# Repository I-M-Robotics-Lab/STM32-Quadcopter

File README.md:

# STM32-Quadcopter: Low-cost Quadcopter Design

### Description

**[Website](https://www.imroboticslab.com/releases)** | **[Documentation](https://www.imroboticslab.com/docs/stm32-quadcopter)**  | **[Community Discord](https://discord.com/invite/WJuUWsy6DJ)** | **[3D Models & Prints](https://makerworld.com/en/models/1695470-quadcopter-3d-printable-stm32-mcu#profileId-1797658)**

This is a quadcopter design based on the STM32F411CEU Blackpill flight controller. The flight controller is compatible with INAV 6.0 firmware. The flight controller uses an MPU6500 for inertial measurements and a BMP280 for altitude sensing, and also supports an optional GPS and magnetometer module.

The frame is composed mostly of 2D parts cut from carbon-fiber sheets. Alternatively, you can 3D-print parts in carbon-fiber-reinforced filaments (PET-CF, PAHT-CF, PA6-CF, PPS-CF), with less-critical components in ABS.

|  |
| --- |

|  |  |
| --- | --- |

|  |  |
| --- | --- |

---

## Table of Contents

- [Introduction](#stm32-quadcopter-low-cost-quadcopter-design)
- [Frame](#frame)
  - [CF Components](#cf-components)
  - [ABS Components](#abs-components)
  - [Mechanical Components BOM](#mechanical-components-bom)
- [Electronics](#electronics)
  - [Electronics BOM](#electronics-bom)
  - [SMD Components](#smd-components)
  - [Pins](#pins)
  - [Sample Diagram](#sample-diagram)
  - [GPS (UART1) Wiring](#gps-uart1-wiring)
  - [Capacitor for Spike Filtering](#capacitor-for-spike-filtering)
- [Firmware](#firmware)
  - [Build](#build)
    - [Prerequisites](#prerequisites)
    - [Clone INAV](#clone-inav)
    - [Add Target](#add-target)
    - [Patch Code](#patch-code)
    - [Build](#build-1)
  - [Flash](#flash)
  - [MPU9250 Issue](#mpu9250-issue)
- [Configuration and Setting Up](#configuration-and-setting-up)

---

## Frame

Use the assembled CAD model in the `3.Models/` folder as a reference to build.

### CF Components

*All files are under `3.Models/`. Add dogbones and tolerances for manufacturability.*

### ABS Components

*Recommend using a 0.4 mm or 0.6 mm high-strength print profile.*

**Mechanical Components BOM**

| Item Name                   | Qty |
|----------------------------|-----|
| M3 Hex Nut                 | 19  |
| M3 x 12mm Button Head Bolt | 2   |
| M3 x 20mm Button Head Bolt | 7   |
| M3 x 20mm Socket Head Bolt | 6   |
| M3 x 30mm Socket Head Bolt | 16  |
| M3 x 35mm Button Head Bolt | 3   |
| M3 x 40mm Button Head Bolt | 1   |
| Nylon Spacer 3-5-11.2            | 8   |
| Nylon Spacer 3-5-20              | 16  |
| Nylon Spacer 3-5-30              | 4   |
| Nylon Spacer 3-5-5               | 2   |

---
## Electronics

**Structure**
```text
1. Electronics/
  ├── Extra/
  │   ├── *.step
  │   └── ...
  ├── Hardware-backups/
  │   └── ...
  ├── Production/           ← Gerber output for fabrication
  │   ├── Hardware-B_Cu.gbl
  │   └── ...
  ├── Hardware.kicad_pcb    ← KiCAD PCB file
  ├── Hardware.kicad_sch    ← KiCAD Schematics file
  ├── Hardware.kicad_pro    ← KiCAD project
  ├── JLCPCB.kicad_dru      ← Rules for JLCPCB manufacturing
  ├── Production.zip        ← Gerber
  └── Schematics.pdf        ← Schematics
```

### Electronics BOM

| Component                        | Qty |
|----------------------------------|:---:|
| RS2205 BLDC Motor                | 4   |
| BLHeli_S 20A ESC                 | 4   |
| 5030R Propeller                  | 2   |
| STM32F411CEU6 “Blackpill”            | 1   |
| MPU6500 / MPU9250 Module            | 1   |
| BMP280 Module        | 1   |
| 330 µF @ 50 V Capacitor           | 1   |
| FS-iA6B Receiver                 | 1   |
| FS-iA6B Transmitter              | 1   |
| Ovonic 1500 mAh 120C 3s Battery | 1   |
| XT60 Connector                   | 1   |

### SMD Components

Gerber files and BOM are available under the electronics folder.

### Pins

### Sample Diagram

*Diagram only; not actual wiring. Please follow the strict pin assignments.*

### GPS (UART1) Wiring

Ensure connectors are wired correctly according to the pinout. Note that RX should connect to TX: `RX1` → GPS `TX`, `TX1` → GPS `RX`.

### Capacitor for Spike Filtering

One or more bulk electrolytic capacitor is recommended to protect against voltage spikes. Use an electrolytic capacitor such as **330 µF @ 50 V** and place it between `VBAT` and `GND` near the input. For extra protection, a **TVS diode** clampeing at ~**12 V** is ideal.

---
## Firmware

### Build

The firmware used is **INAV v6.0.0 ([github link](https://github.com/iNavFlight/inav))**. This project does not support **INAV v7+** currently due to USB issue. If one wants to modify the target file or other configurations of the firmware, they must rebuild the binary. Follow this guide to build:

**Prerequisites**
- CMake ≥ 3.15  
- Ninja  
- gcc-arm-none-eabi toolchain 

**Clone INAV**
```shell
git clone https://github.com/iNavFlight/inav.git
cd inav
git checkout 6.0
```

**Add Target**

Copy the entire `2.Firmware/GYW_BLACKPILL_F411` folder into the local INAV repository under `src/main/target/` so that it ends up as:

```text
inav/
└── src/
    └── main/
        └── target/
            ├──  GYW_BLACKPILL_F411/
            └── ...
```

**Patch Code**

INAV 6.0 doesn’t support a **25 MHz HSE clock** by default, so if your board (like the **Blackpill F411**) uses a 25 MHz crystal, you must update the PLL setup in `src/main/target/system_stm32f4xx.c` as follows:

In `system_stm32f4xx.c`, locate the PLL setup region and modify it as follows:
```diff
#if defined(STM32F40_41xxx) || defined(STM32F427_437xx) || defined(STM32F429_439xx) || defined(STM32F401xx) || defined(STM32F469_479xx) || defined(STM32F446xx) || defined(STM32F410xx) || defined(STM32F411xE)
+   #if HSE_VALUE == 25000000
+       #define PLL_M   25
+   #elif HSE_VALUE == 24000000
-   #if HSE_VALUE == 24000000
        #define PLL_M   24
    #elif HSE_VALUE == 16000000
        #define PLL_M   16
    #elif HSE_VALUE == 8000000
        #define PLL_M   8
    #else
        #error Invalid HSE_VALUE
    #endif
#else
    #error Undefined CPU
#endif
```

**Build**

Ensure that you have installed all dependencies. Inside the inav root repository execute:
```shell
mkdir -p build && cd build
cmake .. -G Ninja \
  -DBOARD=GYW_BLACKPILL_F411 \
  -DCMAKE_TOOLCHAIN_FILE=../tools/cmake/toolchain-arm-none-eabi.cmake
ninja
```

The firmware binary should be at `build/inav_6.0.0_GYW_BLACKPILL_F411.hex`.

### Flash

First, download the **INAV Configurator v6.0.0** from [this link](https://github.com/iNavFlight/inav-configurator/releases/tag/6.0.0). Once installed, launch INAV Configurator and connect to the Blackpill via USB. Cut the **red wire** in the USB cable to prevent it from powering the Blackpill. Instead, power the flight controller using an external **3S battery**.

<div style="text-align: center;">
  
</div>

To enter DFU mode, hold the **BOOT** button on the Blackpill while powering it on. Alternatively, you can press **RESET** while holding the BOOT button. When in DFU mode, the blue LED on the Blackpill will be off, and the board should appear in the INAV Configurator’s drop-down menu as a DFU device. Move to the **Firmware Flasher** tab on the left. Click **Load Firmware**, select the file `inav_6.0.0_GYW_BLACKPILL_F411.hex` (found in the `firmware` folder), then click **Flash Firmware**.

<div style="text-align: center;">
  
</div>

A progress bar will appear during firmware flash.

<div style="text-align: center;">
  
</div>

When the firmware is successfully flashed, click connect. The configuration menu should show up. 
<div style="text-align: center;">
  
</div>

### MPU9250 Issue

If you are using a MPU9250 module, you may encounter the problem that INAV does not recognize the accelerometer. This is due to many boards labeled MPU9250 actually house only an **MPU6500** (omitting or substituting the magnetometer). Since drones often use an external magnetometer, this usually isn’t critical if your accelerometer and gyro (MPU6500) work. 

To identify your chip, read the `WHO_AM_I` register (`0x75`) via I²C (use an Arduino or something similar to do this part). Example Arduino code:
```cpp
#include <Wire.h>
const uint8_t MPU_ADDR     = 0x68; // I²C address
const uint8_t WHO_AM_I_REG = 0x75;
void setup() {
  Serial.begin(115200);
  Wire.begin();
  delay(100);
  Wire.beginTransmission(MPU_ADDR);
  Wire.write(WHO_AM_I_REG);
  if (Wire.endTransmission(false) != 0) {
    Serial.println(F("no device found")); while (1);
  }
  Wire.requestFrom(MPU_ADDR, (uint8_t)1);
  if (Wire.available()) {
    uint8_t id = Wire.read();
    Serial.print(F("WHO_AM_I = 0x"));
    Serial.println(id, HEX);
  } else {
    Serial.println(F("no data returned"));
  }
}
```
If it prints `0x71`, it’s MPU6500; `0x73` indicates MPU9250. 

The current binary file and target is configured for **MPU6500**. To use MPU9250, comment out the block for MPU6500 and uncomment the MPU9250 block in the target file. Rebuild the binary and flash. It looks like this:

```c
#define USE_IMU_MPU9250
#define IMU_MPU9250_ALIGN   CW0_DEG
#define MPU9250_CS_PIN      PB12
#define MPU9250_SPI_BUS     BUS_SPI2
```

---
## Configuration and Setting Up

Follow standard inav configuration procedures.

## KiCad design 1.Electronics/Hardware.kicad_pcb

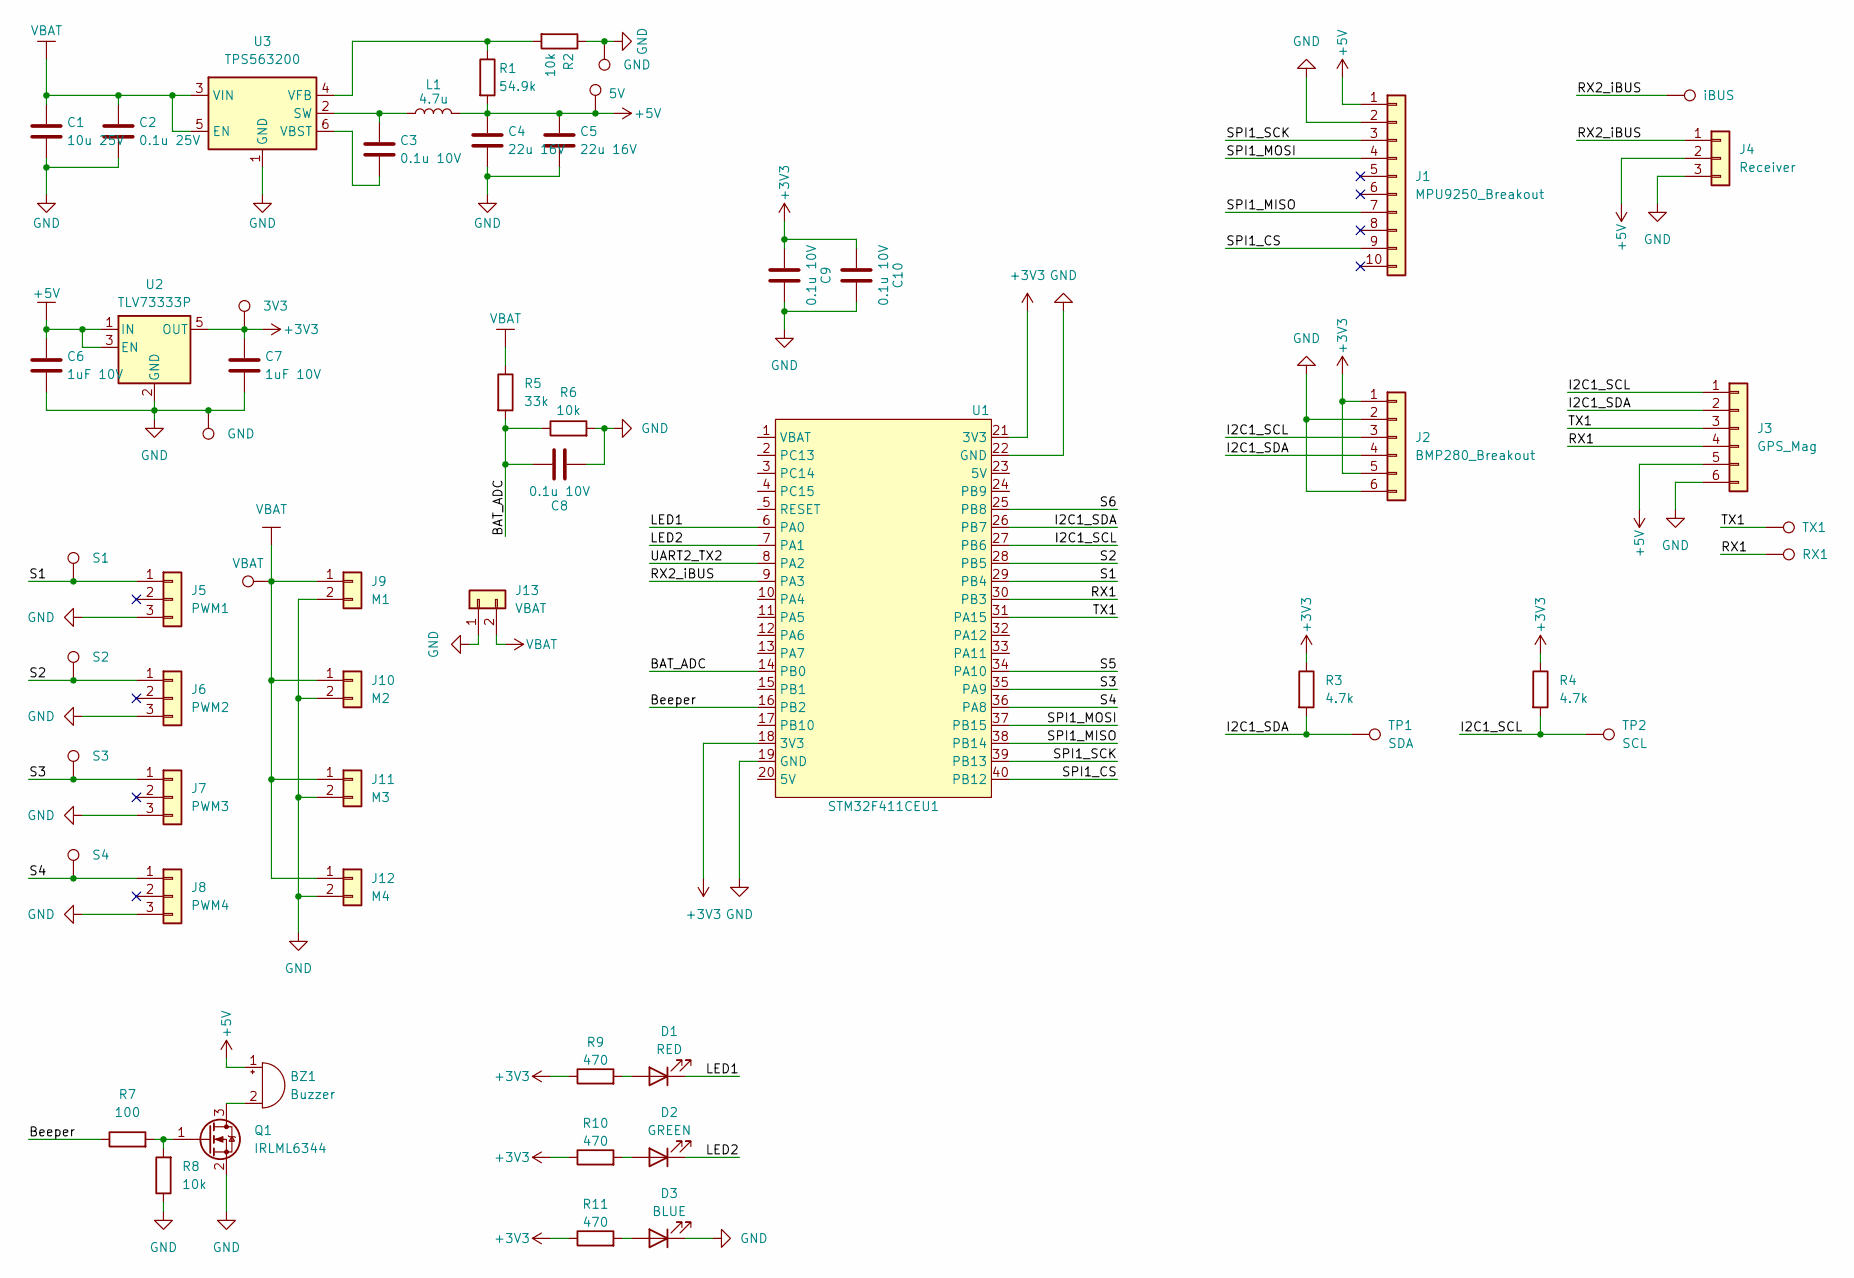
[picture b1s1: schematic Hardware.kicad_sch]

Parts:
BZ1: Buzzer; PinSocket_1x02_P2.54mm_Vertical
C1: 10u 25V; C_0805_2012Metric
C2: 0.1u 25V; C_0805_2012Metric
C3, C8, C9, C10: 0.1u 10V; C_0603_1608Metric
C4, C5: 22u 16V; C_0805_2012Metric
C6, C7: 1uF 10V; C_0603_1608Metric
D1: RED; LED_0805_2012Metric
D2: GREEN; LED_0805_2012Metric
D3: BLUE; LED_0805_2012Metric
J1: MPU9250_Breakout; MPU9250_Mod
J2: BMP280_Breakout; BMP280_Mod
J3: GPS_Mag; JST_SHL_SM06B-SHLS-TF_1x06-1MP_P1.00mm_Horizontal
J4: Receiver; PinHeader_1x03_P2.54mm_Vertical
J5: PWM1; PinHeader_1x03_P2.54mm_Vertical
J6: PWM2; PinHeader_1x03_P2.54mm_Vertical
J7: PWM3; PinHeader_1x03_P2.54mm_Vertical
J8: PWM4; PinHeader_1x03_P2.54mm_Vertical
J9: M1; PAD_1x02_5mm
J10: M2; PAD_1x02_5mm
J11: M3; PAD_1x02_5mm
J12: M4; PAD_1x02_5mm
J13: VBAT; PAD_1x02_5mm
L1: 4.7u; L_Wurth_WE-LHMI-7050
Q1: IRLML6344; SOT-23
R1: 54.9k; R_0603_1608Metric
R2, R6, R8: 10k; R_0603_1608Metric
R3, R4: 4.7k; R_0603_1608Metric
R5: 33k; R_0603_1608Metric
R7: 100; R_0603_1608Metric
R9, R10, R11: 470; R_0603_1608Metric
TP1: SDA; TestPoint_Pad_D1.0mm
TP2: SCL; TestPoint_Pad_D1.0mm
TP3: 5V; TestPoint_Pad_D1.0mm
TP4, TP6: GND; TestPoint_Pad_D1.0mm
TP5: 3V3; TestPoint_Pad_D1.0mm
TP7: TX1; TestPoint_Pad_D1.0mm
TP8: RX1; TestPoint_Pad_D1.0mm
TP9: iBUS; TestPoint_Pad_D1.0mm
TP10: S1; TestPoint_Pad_D1.0mm
TP11: S2; TestPoint_Pad_D1.0mm
TP12: S3; TestPoint_Pad_D1.0mm
TP13: S4; TestPoint_Pad_D1.0mm
TP14: VBAT; TestPoint_Pad_D1.0mm
U1: STM32F411CEU1; Stm32f411ceu_module
U2: TLV73333P; SOT-23-5
U3: TPS563200; SOT-23-6

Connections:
+3V3: C7.1, C9.2, C10.2, J2.1, J2.5, R3.1, R4.1, R9.1, R10.1, R11.1, TP5.1, U1.18 (3V3), U1.21 (3V3), U2.5 (OUT)
+5V: BZ1.1 (+), C4.1, C5.1, C6.1, J1.1, J3.5, J4.2, L1.2, R1.2, TP3.1, U2.1 (IN), U2.3 (EN)
/BAT_ADC: C8.1, R5.2, R6.1, U1.14 (PB0)
/Beeper: R7.1, U1.16 (PB2)
/I2C1_SCL: J2.3, J3.1, R4.2, TP2.1, U1.27 (PB6)
/I2C1_SDA: J2.4, J3.2, R3.2, TP1.1, U1.26 (PB7)
/LED1: D1.1 (K), U1.6 (PA0)
/LED2: D2.1 (K), U1.7 (PA1)
/RX1: J3.4, TP8.1, U1.30 (PB3)
/RX2_iBUS: J4.1, TP9.1, U1.9 (PA3)
/S1: J5.1, TP10.1, U1.29 (PB4)
/S2: J6.1, TP11.1, U1.28 (PB5)
/S3: J7.1, TP12.1, U1.35 (PA9)
/S4: J8.1, TP13.1, U1.36 (PA8)
/S5: U1.34 (PA10)
/S6: U1.25 (PB8)
/SPI1_CS: J1.9, U1.40 (PB12)
/SPI1_MISO: J1.7, U1.38 (PB14)
/SPI1_MOSI: J1.4, U1.37 (PB15)
/SPI1_SCK: J1.3, U1.39 (PB13)
/TX1: J3.3, TP7.1, U1.31 (PA15)
/UART2_TX2: U1.8 (PA2)
GND: C1.2, C2.2, C4.2, C5.2, C6.2, C7.2, C8.2, C9.1, C10.1, D3.1 (K), J1.2, J2.2, J2.6, J3.6, J4.3, J5.3, J6.3, J7.3, J8.3, J9.2, J10.2, J11.2, J12.2, J13.1, Q1.2 (S), R2.1, R6.2, R8.1, TP4.1, TP6.1, U1.19 (GND), U1.22 (GND), U2.2 (GND), U3.1 (GND)
unnamed: BZ1.2 (-), Q1.3 (D)
unnamed: D1.2 (A), R9.2
unnamed: D2.2 (A), R10.2
unnamed: D3.2 (A), R11.2
unnamed: Q1.1 (G), R7.2, R8.2
unnamed: C3.1, L1.1, U3.2 (SW)
unnamed: C3.2, U3.6 (VBST)
unnamed: R1.1, R2.2, U3.4 (VFB)
VBAT: C1.1, C2.1, J9.1, J10.1, J11.1, J12.1, J13.2, R5.1, TP14.1, U3.3 (VIN), U3.5 (EN)

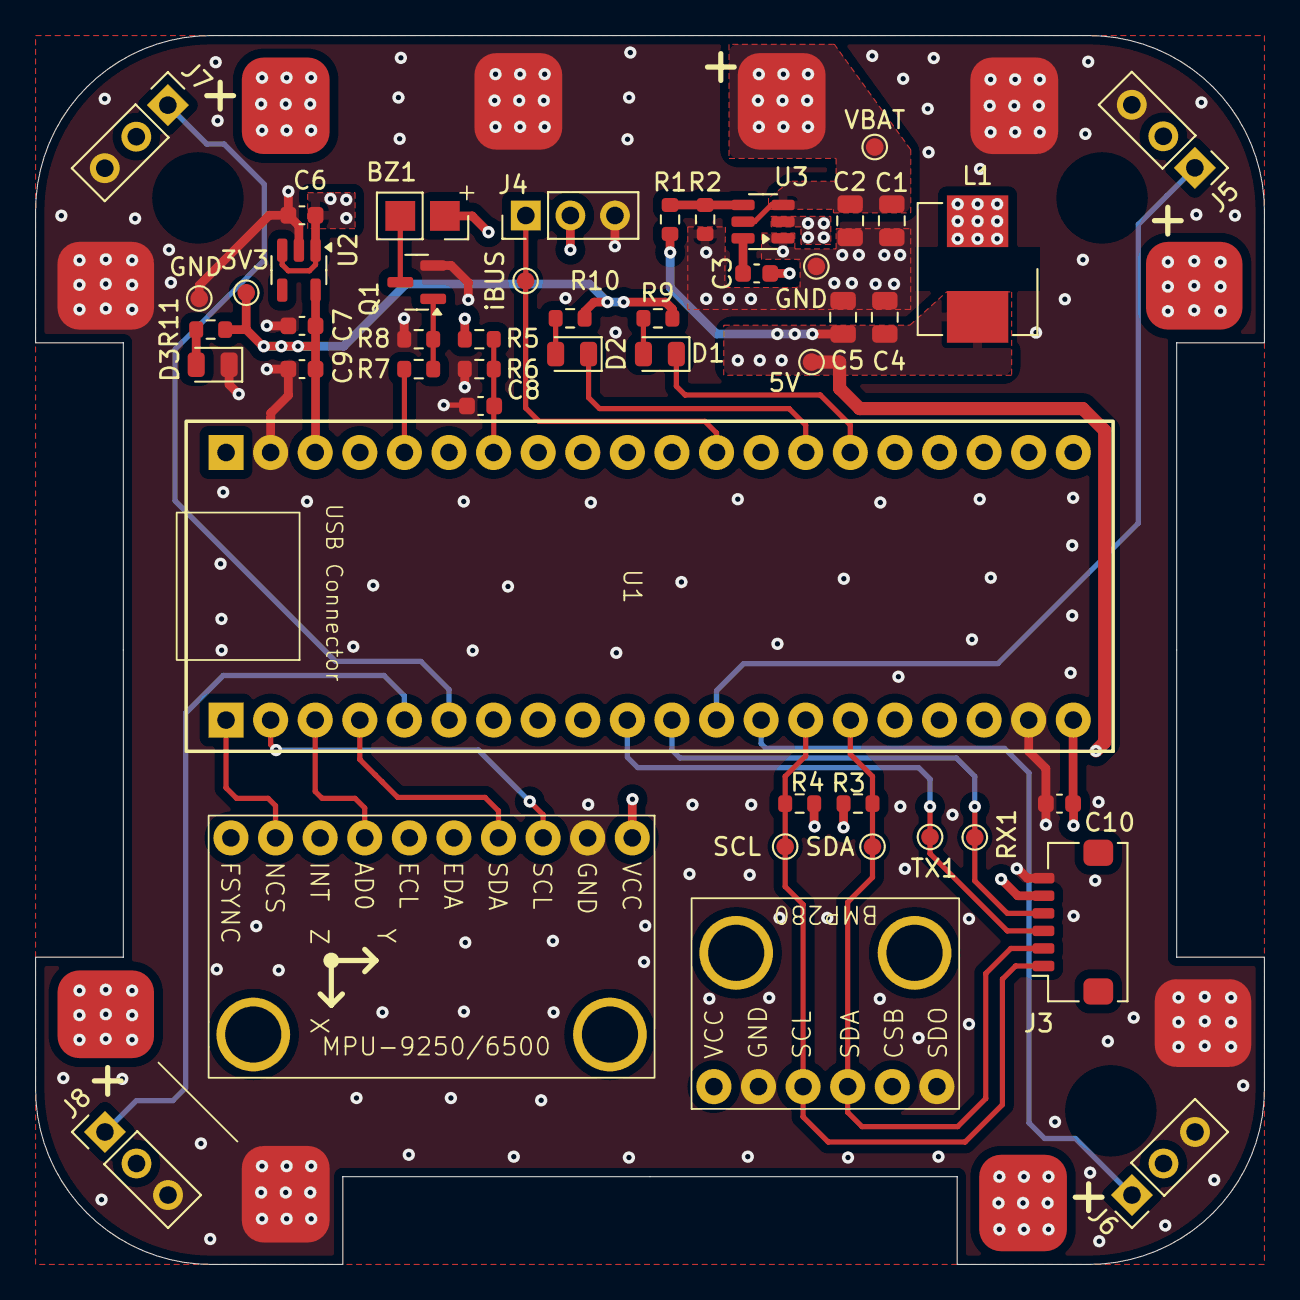
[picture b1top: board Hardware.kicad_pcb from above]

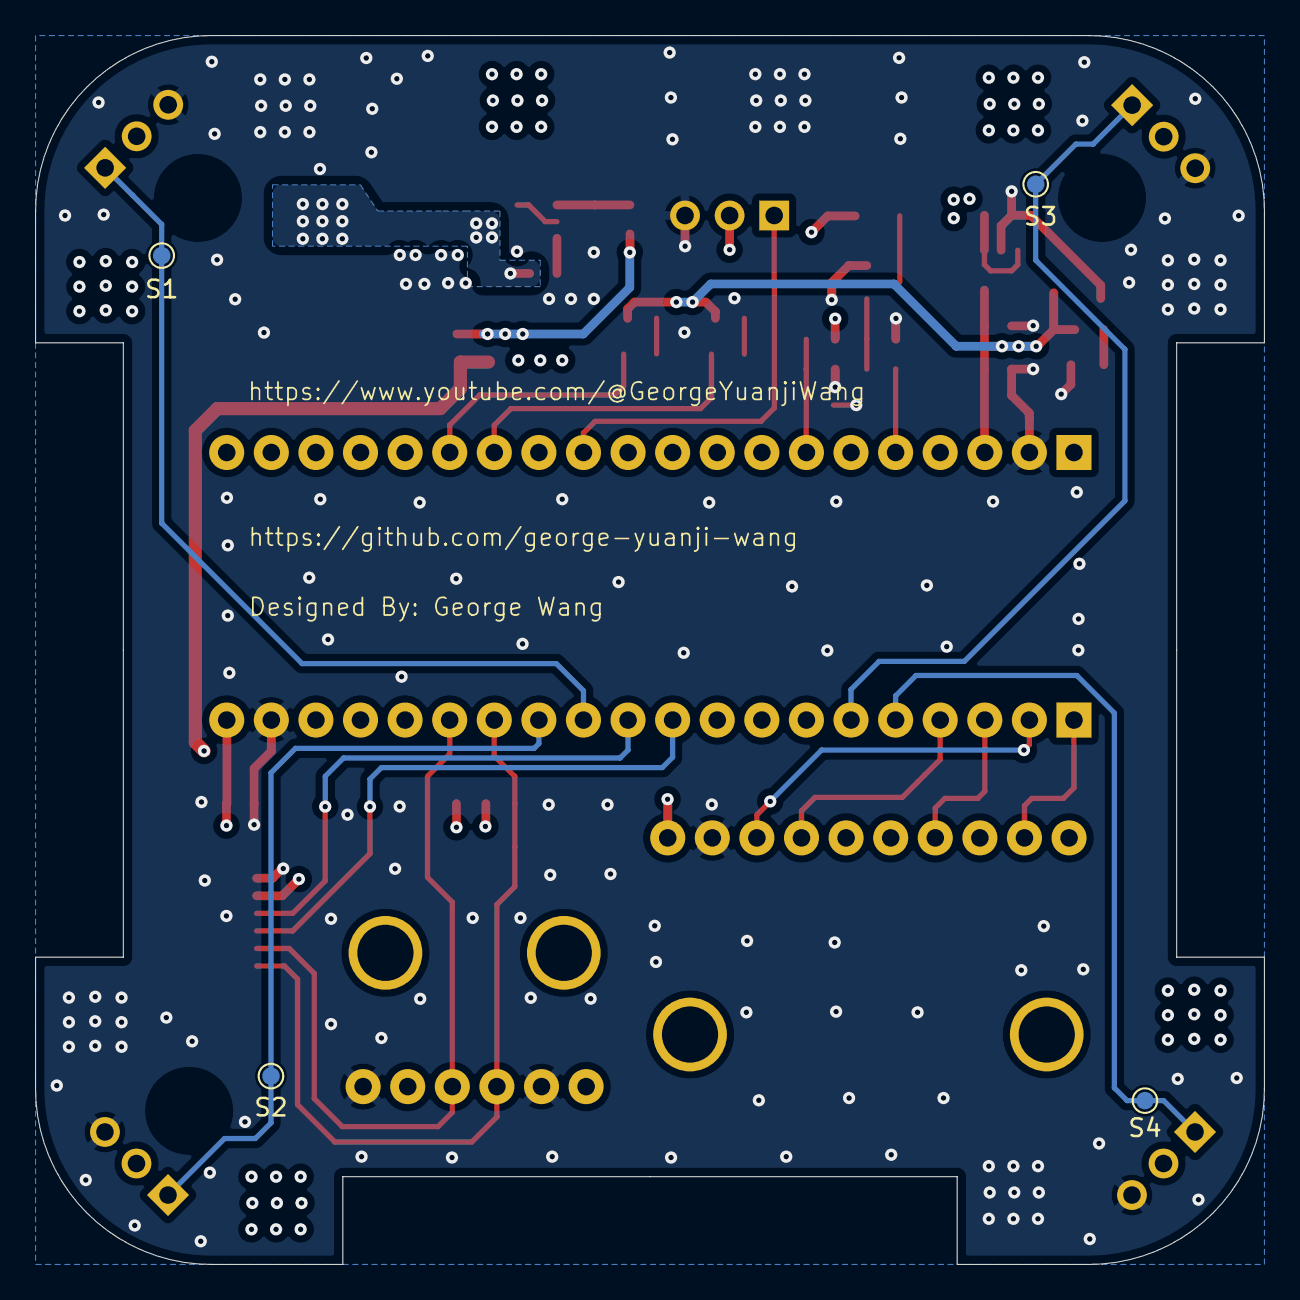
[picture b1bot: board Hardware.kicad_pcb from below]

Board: 4 copper layers, 70.0 x 70.0 mm, 57 parts (4 on the bottom side), 29 nets.

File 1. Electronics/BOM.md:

| Reference       | Value      | Package              | Qty |
|----------------|------------|----------------------|-----|
| C1             | 10u 25V    | 0805                 | 1   |
| C2             | 0.1u 25V   | 0805                 | 1   |
| C3,C8,C9,C10   | 0.1u 10V   | 0603                 | 4   |
| C4             | 22u  16V   | 0805                 | 1   |
| C5             | 22u 16V    | 0805                 | 1   |
| C6,C7          | 1uF 10V    | 0603                 | 2   |
| R1             | 54.9k      | 0603                 | 1   |
| R2,R6,R8       | 10k        | 0603                 | 3   |
| R3,R4          | 4.7k       | 0603                 | 2   |
| R5             | 33k        | 0603                 | 1   |
| R7             | 100        | 0603                 | 1   |
| R9,R10,R11     | 470        | 0603                 | 3   |
| D1             | RED        | 0805 LED             | 1   |
| D2             | GREEN      | 0805 LED             | 1   |
| D3             | BLUE       | 0805 LED             | 1   |
| L1             | 4.7u       | 7050 Inductor        | 1   |
| Q1             | IRLML6344  | SOT-23               | 1   |
| U2             | TLV73333P  | SOT-23-5             | 1   |
| U3             | TPS563200  | SOT-23-6             | 1   |
| U1             | STM32F411CEU1_Pins | STM32F411 Module  | 1   |
| J1             | MPU9250_Pins | MPU9250 Module    | 1   |
| J2             | BMP280_Pins | BMP280 Module      | 1   |
| J3             | JST 6p | JST SH 6P 1.0mm Horiz | 1  |
| J4             | Pin Header 1x3 | Pin Header 1x3 2.54mm| 1   |
| J5             | Pin Header 1x3 | Pin Header 1x3 2.54mm| 1   |
| J6             | Pin Header 1x3 | Pin Header 1x3 2.54mm| 1   |
| J7             | Pin Header 1x3 | Pin Header 1x3 2.54mm| 1   |
| J8             | Pin Header 1x3 | Pin Header 1x3 2.54mm| 1   |

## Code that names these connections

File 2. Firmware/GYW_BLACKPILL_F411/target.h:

#pragma once

#define TARGET_BOARD_IDENTIFIER "GYW_BLACKPILL_F411"
#define USBD_PRODUCT_STRING    "GYW_BLACKPILL_F411"

//LEDs
//#define LED0  PC13 
#define LED0 PA0
#define LED0_INVERTED        
#define LED1   PA1
#define LED1_INVERTED       

#define USE_BUZZER
#define BEEPER PB2 
#define BEEPER_INVERTED      

// *************** SPI2 for MPU9250/MPU6500 **********************
#define USE_SPI
#define USE_SPI_DEVICE_2

#define SPI2_SCK_PIN   PB13
#define SPI2_MISO_PIN  PB14
#define SPI2_MOSI_PIN  PB15

/*
#define USE_IMU_MPU9250
#define IMU_MPU9250_ALIGN   CW0_DEG
#define MPU9250_CS_PIN      PB12
#define MPU9250_SPI_BUS     BUS_SPI2
*/

#define USE_IMU_MPU6500
#define IMU_MPU6500_ALIGN   CW0_DEG
#define MPU6500_CS_PIN      PB12
#define MPU6500_SPI_BUS     BUS_SPI2


// *************** UART *****************************
#define USE_VCP                

#define USE_UART1                         //GPS port
#define UART1_TX_PIN   PA15
#define UART1_RX_PIN   PB3

#define USE_UART2                         //SBUS RC
#define UART2_TX_PIN   PA2                
#define UART2_RX_PIN   PA3

#define SERIAL_PORT_COUNT  3              

#define DEFAULT_RX_TYPE    RX_TYPE_SERIAL
#define SERIALRX_PROVIDER  SERIALRX_SBUS
#define SERIALRX_UART      SERIAL_PORT_USART2

//*************** I2C1 for Baro & Mag ******************
#define USE_I2C
#define USE_I2C_DEVICE_1
#define I2C1_SCL                PB6
#define I2C1_SDA                PB7
#define DEFAULT_I2C_BUS         BUS_I2C1

#define USE_BARO
#define BARO_I2C_BUS            BUS_I2C1
#define USE_BARO_BMP280

#define USE_MAG
#define MAG_I2C_BUS             BUS_I2C1
#define USE_MAG_QMC5883

//*************** ADC (VBAT) *****************************
#define USE_ADC       
#define ADC_INSTANCE            ADC1
#define ADC1_DMA_STREAM         DMA2_Stream0

#define ADC_CHANNEL_1_PIN       PB0

#define VBAT_ADC_CHANNEL        ADC_CHN_1

//***************  OTHERS *************************
#define DEFAULT_FEATURES  ( FEATURE_TX_PROF_SEL | FEATURE_VBAT)

#define TARGET_IO_PORTA  0xffff
#define TARGET_IO_PORTB  0xffff
#define TARGET_IO_PORTC  0xffff
#define TARGET_IO_PORTD  (BIT(2))

#define MAX_PWM_OUTPUT_PORTS  4

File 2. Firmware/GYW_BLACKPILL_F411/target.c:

/*
* This file is part of Cleanflight.
*
* Cleanflight is free software: you can redistribute it and/or modify
* it under the terms of the GNU General Public License as published by
* the Free Software Foundation, either version 3 of the License, or
* (at your option) any later version.
*
* Cleanflight is distributed in the hope that it will be useful,
* but WITHOUT ANY WARRANTY; without even the implied warranty of
* MERCHANTABILITY or FITNESS FOR A PARTICULAR PURPOSE.  See the
* GNU General Public License for more details.
*
* You should have received a copy of the GNU General Public License
* along with Cleanflight.  If not, see <http://www.gnu.org/licenses/>.
*/

#include <stdbool.h>
#include <platform.h>
#include "drivers/bus.h"
#include "drivers/io.h"
#include "drivers/pwm_mapping.h"
#include "drivers/timer.h"
#include "drivers/pinio.h"

timerHardware_t timerHardware[] = {
    //Motor 1 -> PA9
    DEF_TIM(TIM1, CH2, PA9,  TIM_USE_MC_MOTOR, 0, 1),
    //Motor 2 -> PA8 
    DEF_TIM(TIM1, CH1, PA8,  TIM_USE_MC_MOTOR, 0, 1),
    //Motor 3 -> PB4
    DEF_TIM(TIM3, CH1, PB4,  TIM_USE_MC_MOTOR, 0, 0),
    //Motor 4 -> PB5
    DEF_TIM(TIM3, CH2, PB5,  TIM_USE_MC_MOTOR, 0, 0),
};

    

const int timerHardwareCount = sizeof(timerHardware) / sizeof(timerHardware[0]);

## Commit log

2025-07-14 Electronics
2025-07-14 Mechanical Parts
2025-07-15 firmware flash pictures
2025-08-01 almost done readme
    documentations missing inav config procedures
2025-08-01 Table of content
2025-08-13 pictures
2025-08-13 fix pic
2025-08-13 pic last
2025-08-13 mf files
2025-11-06 Add Discord link to README
    Added Discord link for community engagement.
2025-11-13 new license
2025-11-13 readme

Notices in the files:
README.md:
License: GPL v3
